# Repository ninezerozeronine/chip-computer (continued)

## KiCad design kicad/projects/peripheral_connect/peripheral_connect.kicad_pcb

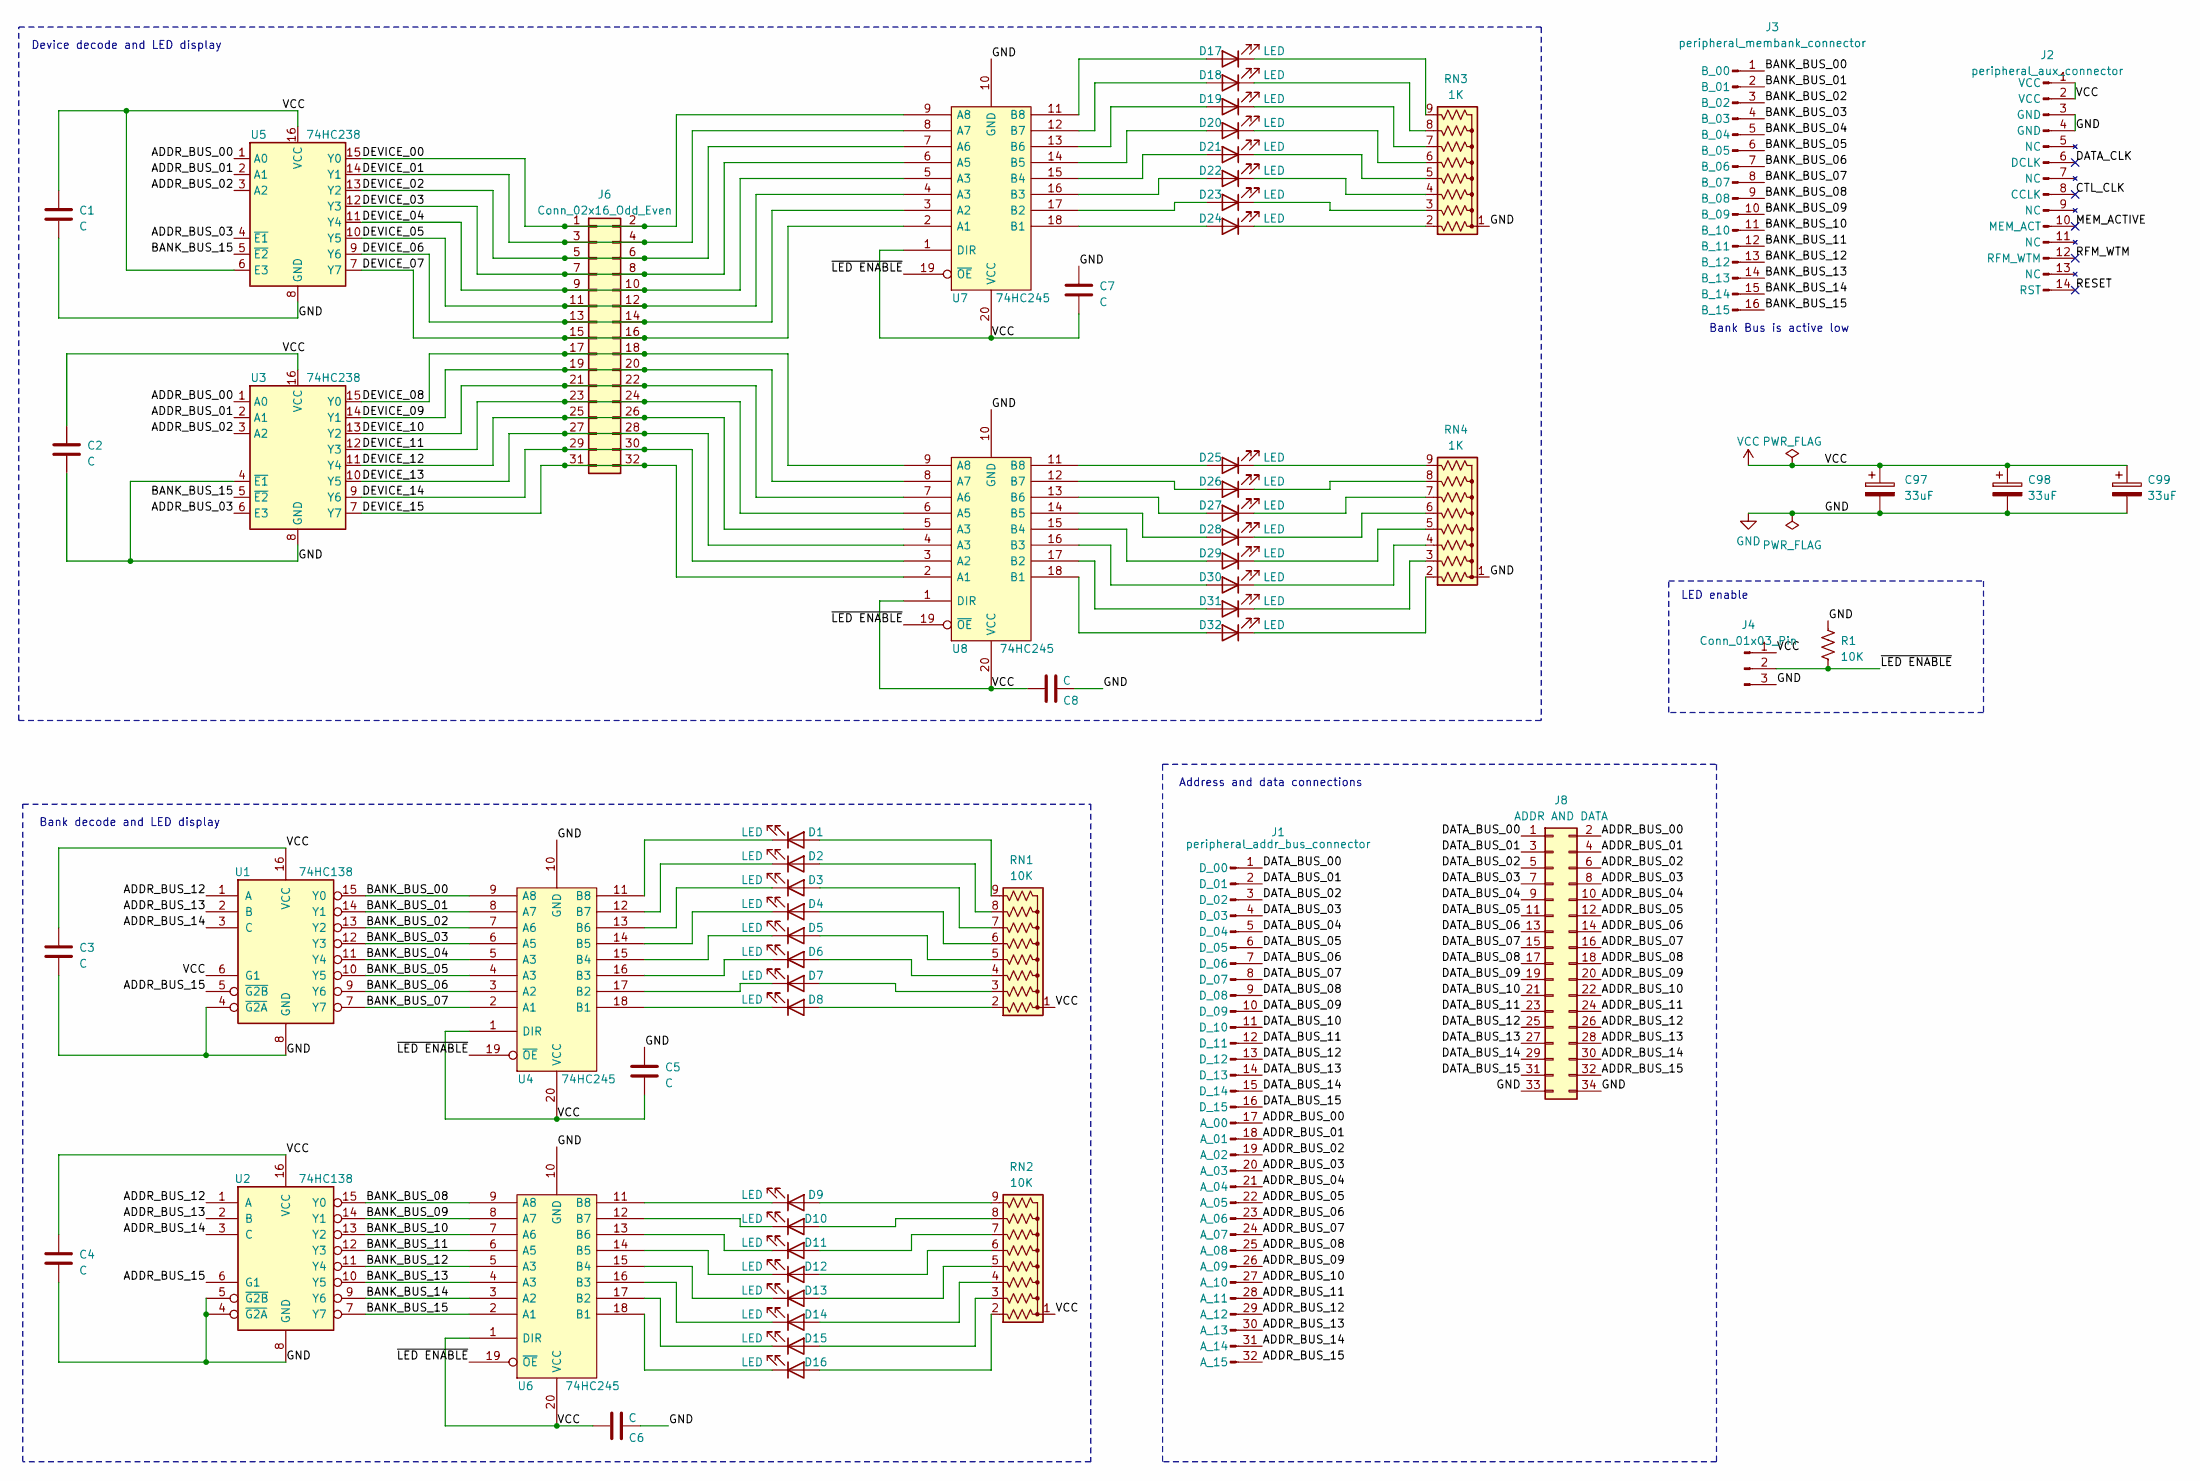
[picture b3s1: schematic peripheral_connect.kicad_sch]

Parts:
C1, C2, C3, C4, C5, C6, C7, C8: C; C_Disc_D5.0mm_W2.5mm_P5.00mm
C97, C98, C99: 33uF; CP_Radial_D6.3mm_P2.50mm
D1, D2, D3, D4, D5, D6, D7, D8, D9, D10, D11, D12, D13, D14, D15, D16, D17, D18, D19, D20, D21, D22, D23, D24, D25, D26, D27, D28, D29, D30, D31, D32: LED; LED_D5.0mm_Horizontal_O3.81mm_Z3.0mm
J1: peripheral_addr_bus_connector; peripheral-backplane-data-addr-anno
J2: peripheral_aux_connector; peripheral-backplane-aux
J3: peripheral_membank_connector; peripheral-backplane-membank
J4: Conn_01x03_Pin; PinHeader_1x03_P2.54mm_Horizontal
J6: Conn_02x16_Odd_Even; PinSocket_2x16_P2.54mm_Horizontal
J8: ADDR AND DATA; PinSocket_2x17_P2.54mm_Horizontal
R1: 10K; R_Axial_DIN0207_L6.3mm_D2.5mm_P10.16mm_Horizontal
RN1, RN2: 10K; R_Array_SIP9
RN3, RN4: 1K; R_Array_SIP9
U1, U2: 74HC138; DIP-16_W7.62mm_Socket
U3, U5: 74HC238; DIP-16_W7.62mm_Socket
U4, U6, U7, U8: 74HC245; DIP-20_W7.62mm_Socket

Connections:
/ADDR_BUS_00: J1.17 (A_00), J8.2, U3.1 (A0), U5.1 (A0)
/ADDR_BUS_01: J1.18 (A_01), J8.4, U3.2 (A1), U5.2 (A1)
/ADDR_BUS_02: J1.19 (A_02), J8.6, U3.3 (A2), U5.3 (A2)
/ADDR_BUS_03: J1.20 (A_03), J8.8, U3.6 (E3), U5.4 (~E1)
/ADDR_BUS_04: J1.21 (A_04), J8.10
/ADDR_BUS_05: J1.22 (A_05), J8.12
/ADDR_BUS_06: J1.23 (A_06), J8.14
/ADDR_BUS_07: J1.24 (A_07), J8.16
/ADDR_BUS_08: J1.25 (A_08), J8.18
/ADDR_BUS_09: J1.26 (A_09), J8.20
/ADDR_BUS_10: J1.27 (A_10), J8.22
/ADDR_BUS_11: J1.28 (A_11), J8.24
/ADDR_BUS_12: J1.29 (A_12), J8.26, U1.1 (A), U2.1 (A)
/ADDR_BUS_13: J1.30 (A_13), J8.28, U1.2 (B), U2.2 (B)
/ADDR_BUS_14: J1.31 (A_14), J8.30, U1.3 (C), U2.3 (C)
/ADDR_BUS_15: J1.32 (A_15), J8.32, U1.5 (~G2B), U2.6 (G1)
/BANK_BUS_00: J3.1 (B_00), U1.15 (Y0), U4.9 (A8)
/BANK_BUS_01: J3.2 (B_01), U1.14 (Y1), U4.8 (A7)
/BANK_BUS_02: J3.3 (B_02), U1.13 (Y2), U4.7 (A6)
/BANK_BUS_03: J3.4 (B_03), U1.12 (Y3), U4.6 (A5)
/BANK_BUS_04: J3.5 (B_04), U1.11 (Y4), U4.5 (A3)
/BANK_BUS_05: J3.6 (B_05), U1.10 (Y5), U4.4 (A3)
/BANK_BUS_06: J3.7 (B_06), U1.9 (Y6), U4.3 (A2)
/BANK_BUS_07: J3.8 (B_07), U1.7 (Y7), U4.2 (A1)
/BANK_BUS_08: J3.9 (B_08), U2.15 (Y0), U6.9 (A8)
/BANK_BUS_09: J3.10 (B_09), U2.14 (Y1), U6.8 (A7)
/BANK_BUS_10: J3.11 (B_10), U2.13 (Y2), U6.7 (A6)
/BANK_BUS_11: J3.12 (B_11), U2.12 (Y3), U6.6 (A5)
/BANK_BUS_12: J3.13 (B_12), U2.11 (Y4), U6.5 (A3)
/BANK_BUS_13: J3.14 (B_13), U2.10 (Y5), U6.4 (A3)
/BANK_BUS_14: J3.15 (B_14), U2.9 (Y6), U6.3 (A2)
/BANK_BUS_15: J3.16 (B_15), U2.7 (Y7), U3.5 (~E2), U5.5 (~E2), U6.2 (A1)
/CTL_CLK: J2.8 (CCLK)
/DATA_BUS_00: J1.1 (D_00), J8.1
/DATA_BUS_01: J1.2 (D_01), J8.3
/DATA_BUS_02: J1.3 (D_02), J8.5
/DATA_BUS_03: J1.4 (D_03), J8.7
/DATA_BUS_04: J1.5 (D_04), J8.9
/DATA_BUS_05: J1.6 (D_05), J8.11
/DATA_BUS_06: J1.7 (D_06), J8.13
/DATA_BUS_07: J1.8 (D_07), J8.15
/DATA_BUS_08: J1.9 (D_08), J8.17
/DATA_BUS_09: J1.10 (D_09), J8.19
/DATA_BUS_10: J1.11 (D_10), J8.21
/DATA_BUS_11: J1.12 (D_11), J8.23
/DATA_BUS_12: J1.13 (D_12), J8.25
/DATA_BUS_13: J1.14 (D_13), J8.27
/DATA_BUS_14: J1.15 (D_14), J8.29
/DATA_BUS_15: J1.16 (D_15), J8.31
/DATA_CLK: J2.6 (DCLK)
/DEVICE_00: J6.1, J6.2, U5.15 (Y0), U7.9 (A8)
/DEVICE_01: J6.3, J6.4, U5.14 (Y1), U7.8 (A7)
/DEVICE_02: J6.5, J6.6, U5.13 (Y2), U7.7 (A6)
/DEVICE_03: J6.7, J6.8, U5.12 (Y3), U7.6 (A5)
/DEVICE_04: J6.9, J6.10, U5.11 (Y4), U7.5 (A3)
/DEVICE_05: J6.11, J6.12, U5.10 (Y5), U7.4 (A3)
/DEVICE_06: J6.13, J6.14, U5.9 (Y6), U7.3 (A2)
/DEVICE_07: J6.15, J6.16, U5.7 (Y7), U7.2 (A1)
/DEVICE_08: J6.17, J6.18, U3.15 (Y0), U8.9 (A8)
/DEVICE_09: J6.19, J6.20, U3.14 (Y1), U8.8 (A7)
/DEVICE_10: J6.21, J6.22, U3.13 (Y2), U8.7 (A6)
/DEVICE_11: J6.23, J6.24, U3.12 (Y3), U8.6 (A5)
/DEVICE_12: J6.25, J6.26, U3.11 (Y4), U8.5 (A3)
/DEVICE_13: J6.27, J6.28, U3.10 (Y5), U8.4 (A3)
/DEVICE_14: J6.29, J6.30, U3.9 (Y6), U8.3 (A2)
/DEVICE_15: J6.31, J6.32, U3.7 (Y7), U8.2 (A1)
/MEM_ACTIVE: J2.10 (MEM_ACT)
/RESET: J2.14 (RST)
/RFM_WTM: J2.12 (RFM_WTM)
/~LED ENABLE: J4.2, R1.1, U4.19 (~OE), U6.19 (~OE), U7.19 (~OE), U8.19 (~OE)
GND: C1.2, C2.2, C3.2, C4.2, C5.2, C6.1, C7.2, C8.1, C97.2, C98.2, C99.2, J2.3 (GND), J2.4 (GND), J4.3, J8.33, J8.34, R1.2, RN3.1 (common), RN4.1 (common), U1.4 (~G2A), U1.8 (GND), U2.4 (~G2A), U2.5 (~G2B), U2.8 (GND), U3.4 (~E1), U3.8 (GND), U4.10 (GND), U5.8 (GND), U6.10 (GND), U7.10 (GND), U8.10 (GND)
unnamed: D1.2 (A), RN1.9 (R8)
unnamed: D1.1 (K), U4.11 (B8)
unnamed: D2.2 (A), RN1.8 (R7)
unnamed: D2.1 (K), U4.12 (B7)
unnamed: D3.2 (A), RN1.7 (R6)
unnamed: D3.1 (K), U4.13 (B6)
unnamed: D4.2 (A), RN1.6 (R5)
unnamed: D4.1 (K), U4.14 (B5)
unnamed: D5.2 (A), RN1.5 (R4)
unnamed: D5.1 (K), U4.15 (B4)
unnamed: D6.2 (A), RN1.4 (R3)
unnamed: D6.1 (K), U4.16 (B3)
unnamed: D7.2 (A), RN1.3 (R2)
unnamed: D7.1 (K), U4.17 (B2)
unnamed: D8.2 (A), RN1.2 (R1)
unnamed: D8.1 (K), U4.18 (B1)
unnamed: D9.2 (A), RN2.9 (R8)
unnamed: D9.1 (K), U6.11 (B8)
unnamed: D10.2 (A), RN2.8 (R7)
unnamed: D10.1 (K), U6.12 (B7)
unnamed: D11.2 (A), RN2.7 (R6)
unnamed: D11.1 (K), U6.13 (B6)
unnamed: D12.2 (A), RN2.6 (R5)
unnamed: D12.1 (K), U6.14 (B5)
unnamed: D13.2 (A), RN2.5 (R4)
unnamed: D13.1 (K), U6.15 (B4)
unnamed: D14.2 (A), RN2.4 (R3)
unnamed: D14.1 (K), U6.16 (B3)
unnamed: D15.2 (A), RN2.3 (R2)
unnamed: D15.1 (K), U6.17 (B2)
unnamed: D16.2 (A), RN2.2 (R1)
unnamed: D16.1 (K), U6.18 (B1)
unnamed: D17.2 (A), U7.11 (B8)
unnamed: D17.1 (K), RN3.9 (R8)
unnamed: D18.2 (A), U7.12 (B7)
unnamed: D18.1 (K), RN3.8 (R7)
unnamed: D19.2 (A), U7.13 (B6)
unnamed: D19.1 (K), RN3.7 (R6)
unnamed: D20.2 (A), U7.14 (B5)
unnamed: D20.1 (K), RN3.6 (R5)
unnamed: D21.2 (A), U7.15 (B4)
unnamed: D21.1 (K), RN3.5 (R4)
unnamed: D22.2 (A), U7.16 (B3)
unnamed: D22.1 (K), RN3.4 (R3)
unnamed: D23.2 (A), U7.17 (B2)
unnamed: D23.1 (K), RN3.3 (R2)
unnamed: D24.2 (A), U7.18 (B1)
unnamed: D24.1 (K), RN3.2 (R1)
unnamed: D25.2 (A), U8.11 (B8)
unnamed: D25.1 (K), RN4.9 (R8)
unnamed: D26.2 (A), U8.12 (B7)
unnamed: D26.1 (K), RN4.8 (R7)
unnamed: D27.2 (A), U8.13 (B6)
unnamed: D27.1 (K), RN4.7 (R6)
unnamed: D28.2 (A), U8.14 (B5)
unnamed: D28.1 (K), RN4.6 (R5)
unnamed: D29.2 (A), U8.15 (B4)
unnamed: D29.1 (K), RN4.5 (R4)
unnamed: D30.2 (A), U8.16 (B3)
unnamed: D30.1 (K), RN4.4 (R3)
unnamed: D31.2 (A), U8.17 (B2)
unnamed: D31.1 (K), RN4.3 (R2)
unnamed: D32.2 (A), U8.18 (B1)
unnamed: D32.1 (K), RN4.2 (R1)
VCC: C1.1, C2.1, C3.1, C4.1, C5.1, C6.2, C7.1, C8.2, C97.1, C98.1, C99.1, J2.1 (VCC), J2.2 (VCC), J4.1, RN1.1 (common), RN2.1 (common), U1.6 (G1), U1.16 (VCC), U2.16 (VCC), U3.16 (VCC), U4.1 (DIR), U4.20 (VCC), U5.6 (E3), U5.16 (VCC), U6.1 (DIR), U6.20 (VCC), U7.1 (DIR), U7.20 (VCC), U8.1 (DIR), U8.20 (VCC)

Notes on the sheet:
Address and data connections
Bank decode and LED display
Device decode and LED display
LED enable
Bank Bus is active low

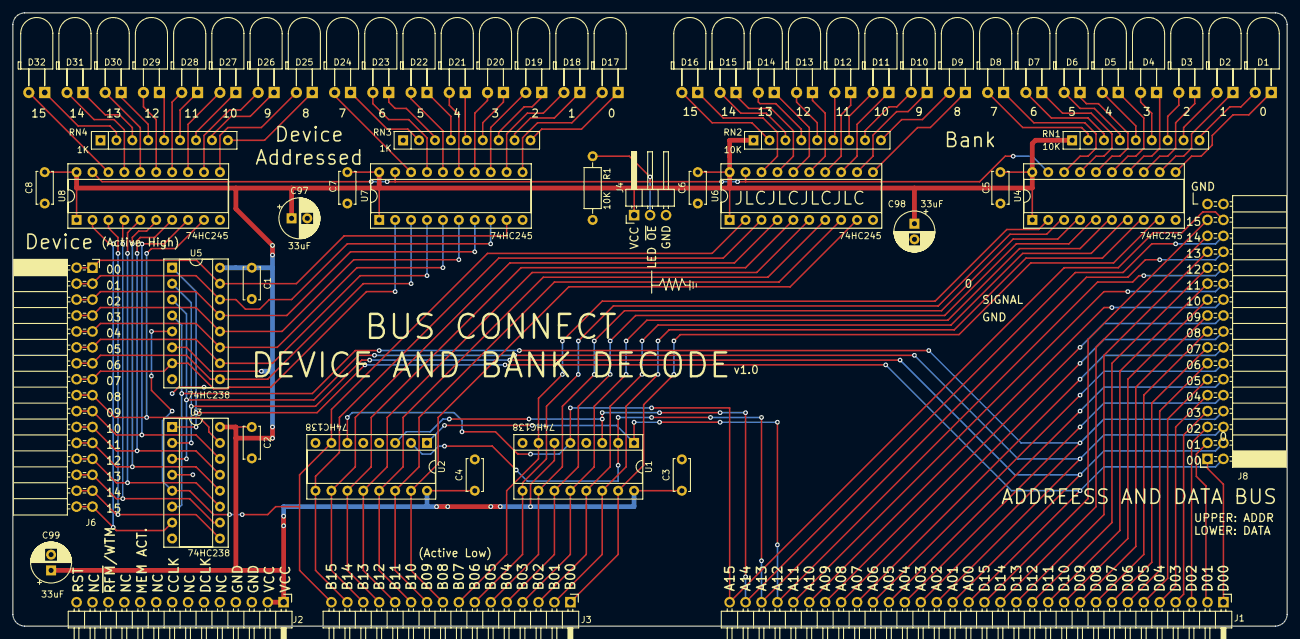
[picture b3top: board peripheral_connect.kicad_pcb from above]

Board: 2 copper layers, 203.2 x 97.8 mm, 62 parts (0 on the bottom side), 131 nets.

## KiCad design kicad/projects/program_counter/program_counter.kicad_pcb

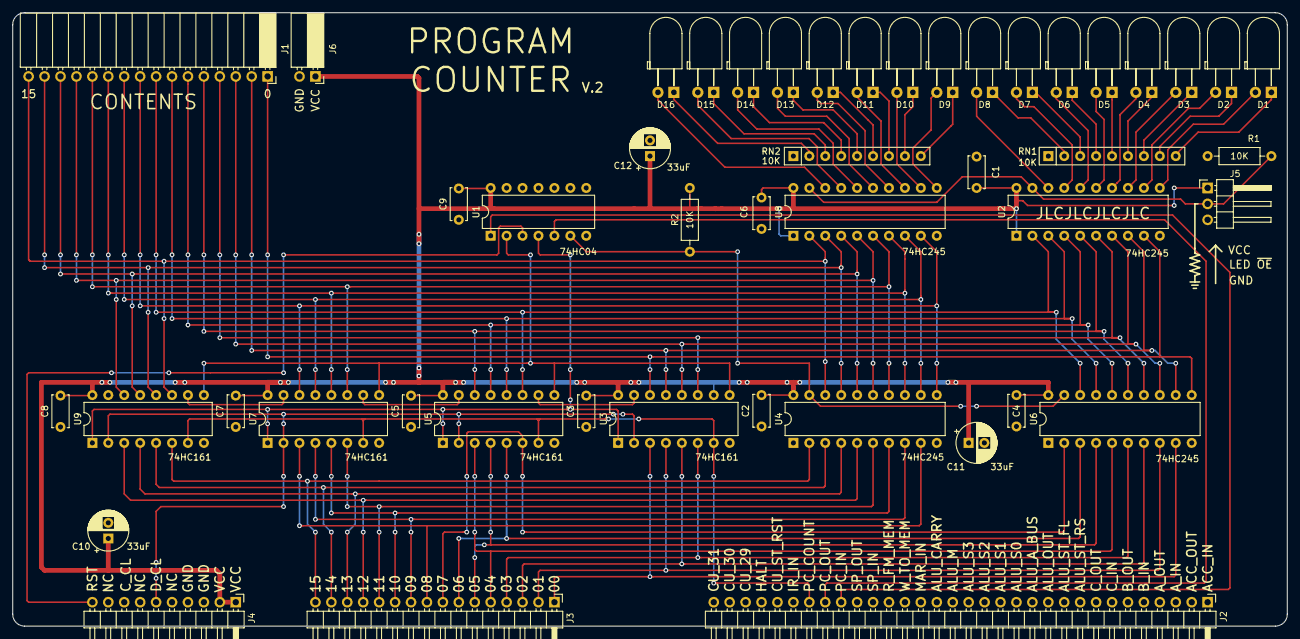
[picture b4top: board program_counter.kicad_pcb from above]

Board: 2 copper layers, 203.2 x 97.8 mm, 47 parts (0 on the bottom side), 78 nets.

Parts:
C1, C2, C3, C4, C5, C6, C7, C8, C9: 0.1uF; C_Disc_D5.0mm_W2.5mm_P5.00mm
C10, C11, C12: 33uF; CP_Radial_D6.3mm_P2.50mm
D1, D2, D3, D4, D5, D6, D7, D8, D9, D10, D11, D12, D13, D14, D15, D16: LED; LED_D5.0mm_Horizontal_O3.81mm_Z3.0mm
J1: Conn_01x16_Female; PinSocket_1x16_P2.54mm_Horizontal
J2: Control_signal_backplane; backplane-connector-single-row-annotated
J3: Bus_connection; bus-connection
J4: Aux_connection; aux-connection
J5: LED_CONTROL; PinHeader_1x03_P2.54mm_Horizontal
J6: TOP_POWER; PinSocket_1x02_P2.54mm_Horizontal
R1, R2: 10K; R_Axial_DIN0207_L6.3mm_D2.5mm_P10.16mm_Horizontal
RN1, RN2: 10K; R_Array_SIP9
U1: 74HC04; DIP-14_W7.62mm
U2, U4, U6, U8: 74HC245; DIP-20_W7.62mm
U3, U5, U7, U9: 74HC161; DIP-16_W7.62mm

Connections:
/BUS_00: J3.1, U3.3, U6.9
/BUS_01: J3.2, U3.4, U6.8
/BUS_02: J3.3, U3.5, U6.7
/BUS_03: J3.4, U3.6, U6.6
/BUS_04: J3.5, U5.3, U6.5
/BUS_05: J3.6, U5.4, U6.4
/BUS_06: J3.7, U5.5, U6.3
/BUS_07: J3.8, U5.6, U6.2
/BUS_08: J3.9, U4.9, U7.3
/BUS_09: J3.10, U4.8, U7.4
/BUS_10: J3.11, U4.7, U7.5
/BUS_11: J3.12, U4.6, U7.6
/BUS_12: J3.13, U4.5, U9.3
/BUS_13: J3.14, U4.4, U9.4
/BUS_14: J3.15, U4.3, U9.5
/BUS_15: J3.16, U4.2, U9.6
/CTNT_00: J1.1, U2.9, U3.14, U6.11
/CTNT_01: J1.2, U2.8, U3.13, U6.12
/CTNT_02: J1.3, U2.7, U3.12, U6.13
/CTNT_03: J1.4, U2.6, U3.11, U6.14
/CTNT_04: J1.5, U2.5, U5.14, U6.15
/CTNT_05: J1.6, U2.4, U5.13, U6.16
/CTNT_06: J1.7, U2.3, U5.12, U6.17
/CTNT_07: J1.8, U2.2, U5.11, U6.18
/CTNT_08: J1.9, U4.11, U7.14, U8.9
/CTNT_09: J1.10, U4.12, U7.13, U8.8
/CTNT_10: J1.11, U4.13, U7.12, U8.7
/CTNT_11: J1.12, U4.14, U7.11, U8.6
/CTNT_12: J1.13, U4.15, U8.5, U9.14
/CTNT_13: J1.14, U4.16, U8.4, U9.13
/CTNT_14: J1.15, U4.17, U8.3, U9.12
/CTNT_15: J1.16, U4.18, U8.2, U9.11
/DATA_CLK: J4.6, U3.2, U5.2, U7.2, U9.2
/LED_CONTROL: J5.2, R1.1, U2.19, U8.19
/PC_COUNT: J2.26, U3.7, U5.7, U7.7, U9.7
/PC_IN: J2.24, U1.1
/PC_OUT: J2.25, U1.5
/RESET: J4.10, U1.3
/~PC_IN: U1.2, U3.9, U5.9, U7.9, U9.9
/~PC_OUT: R2.1, U1.6, U4.19, U6.19
/~RESET: U1.4, U3.1, U5.1, U7.1, U9.1
GND: C1.2, C2.2, C3.1, C4.2, C5.1, C6.2, C7.1, C8.1, C9.1, C10.2, C11.2, C12.2, J4.3, J4.4, J5.3, J6.2, R1.2, RN1.1, RN2.1, U1.7, U1.9, U1.11, U1.13, U2.10, U3.8, U4.1, U4.10, U5.8, U6.1, U6.10, U7.8, U8.10, U9.8
unnamed: D1.1, RN1.9
unnamed: D1.2, U2.11
unnamed: D2.1, RN1.8
unnamed: D2.2, U2.12
unnamed: D3.1, RN1.7
unnamed: D3.2, U2.13
unnamed: D4.1, RN1.6
unnamed: D4.2, U2.14
unnamed: D5.1, RN1.5
unnamed: D5.2, U2.15
unnamed: D6.1, RN1.4
unnamed: D6.2, U2.16
unnamed: D7.1, RN1.3
unnamed: D7.2, U2.17
unnamed: D8.1, RN1.2
unnamed: D8.2, U2.18
unnamed: D9.1, RN2.9
unnamed: D9.2, U8.11
unnamed: D10.1, RN2.8
unnamed: D10.2, U8.12
unnamed: D11.1, RN2.7
unnamed: D11.2, U8.13
unnamed: D12.1, RN2.6
unnamed: D12.2, U8.14
unnamed: D13.1, RN2.5
unnamed: D13.2, U8.15
unnamed: D14.1, RN2.4
unnamed: D14.2, U8.16
unnamed: D15.1, RN2.3
unnamed: D15.2, U8.17
unnamed: D16.1, RN2.2
unnamed: D16.2, U8.18
unnamed: U3.15, U5.10
unnamed: U5.15, U7.10
unnamed: U7.15, U9.10
VCC: C1.1, C2.1, C3.2, C4.1, C5.2, C6.1, C7.2, C8.2, C9.2, C10.1, C11.1, C12.1, J4.1, J4.2, J5.1, J6.1, R2.2, U1.14, U2.1, U2.20, U3.10, U3.16, U4.20, U5.16, U6.20, U7.16, U8.1, U8.20, U9.16

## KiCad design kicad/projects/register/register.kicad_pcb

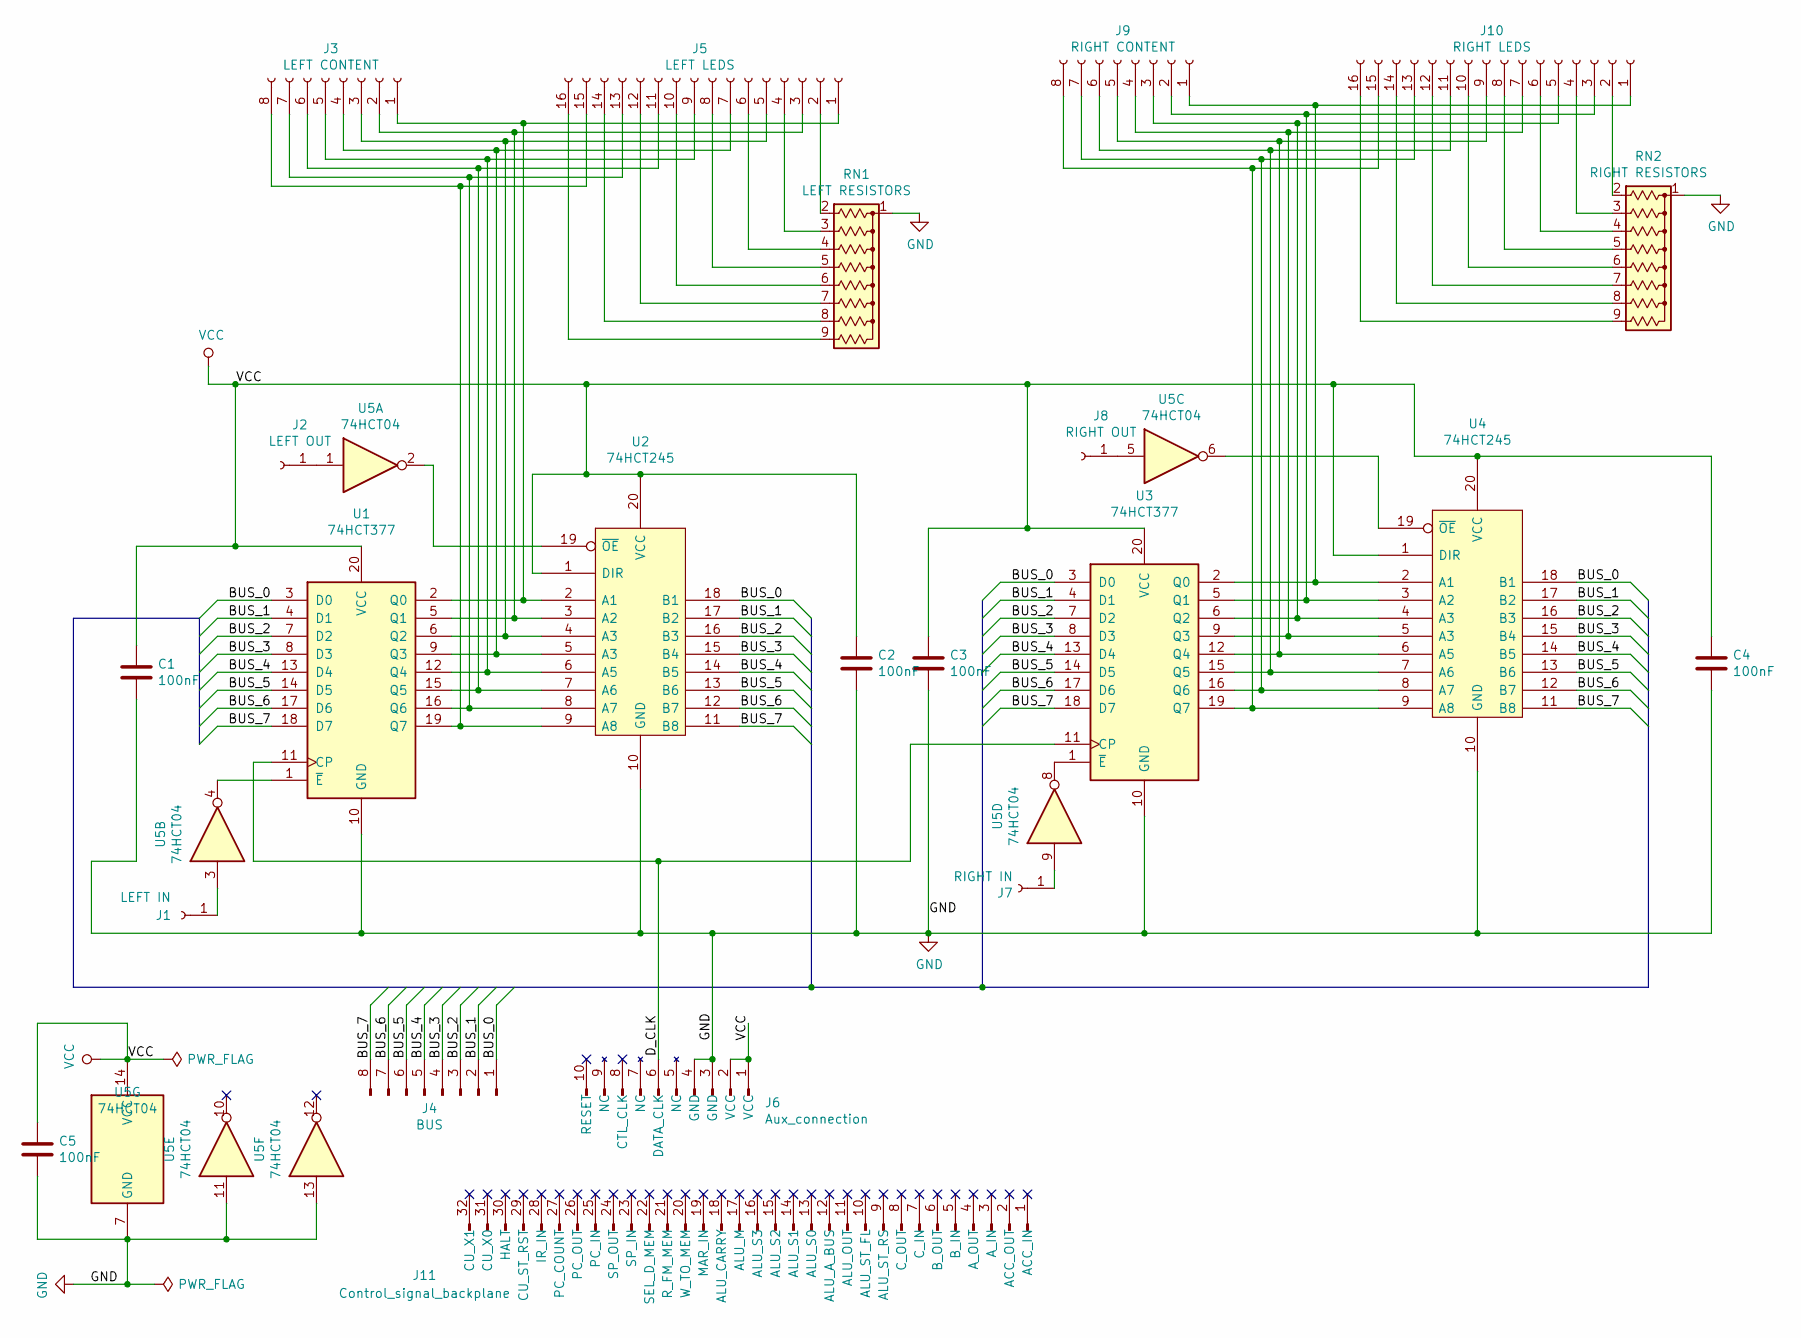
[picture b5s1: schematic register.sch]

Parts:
C1, C2, C3, C4, C5: 100nF; C_Disc_D4.7mm_W2.5mm_P5.00mm
J1: LEFT IN; SolderWirePad_1x01_Drill0.8mm
J2: LEFT OUT; SolderWirePad_1x01_Drill0.8mm
J3: LEFT CONTENT; PinSocket_1x08_P2.54mm_Horizontal
J4: BUS; PinHeader_1x08_P2.54mm_Horizontal
J5: LEFT LEDS; PinSocket_1x16_P2.54mm_Horizontal
J6: Aux_connection; PinHeader_1x10_P2.54mm_Horizontal
J7: RIGHT IN; SolderWirePad_1x01_Drill0.8mm
J8: RIGHT OUT; SolderWirePad_1x01_Drill0.8mm
J9: RIGHT CONTENT; PinSocket_1x08_P2.54mm_Horizontal
J10: RIGHT LEDS; PinSocket_1x16_P2.54mm_Horizontal
J11: Control_signal_backplane; backplane-connector
RN1: LEFT RESISTORS; R_Array_SIP9
RN2: RIGHT RESISTORS; R_Array_SIP9
U1, U3: 74HCT377; DIP-20_W7.62mm_Socket
U2, U4: 74HCT245; DIP-20_W7.62mm_Socket
U5: 74HCT04; DIP-14_W7.62mm_Socket

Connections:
/BUS_0: J4.1, U1.3 (D0), U2.18 (B1), U3.3 (D0), U4.18 (B1)
/BUS_1: J4.2, U1.4 (D1), U2.17 (B2), U3.4 (D1), U4.17 (B2)
/BUS_2: J4.3, U1.7 (D2), U2.16 (B3), U3.7 (D2), U4.16 (B3)
/BUS_3: J4.4, U1.8 (D3), U2.15 (B4), U3.8 (D3), U4.15 (B4)
/BUS_4: J4.5, U1.13 (D4), U2.14 (B5), U3.13 (D4), U4.14 (B5)
/BUS_5: J4.6, U1.14 (D5), U2.13 (B6), U3.14 (D5), U4.13 (B6)
/BUS_6: J4.7, U1.17 (D6), U2.12 (B7), U3.17 (D6), U4.12 (B7)
/BUS_7: J4.8, U1.18 (D7), U2.11 (B8), U3.18 (D7), U4.11 (B8)
/D_CLK: J6.6 (DATA_CLK), U1.11 (CP), U3.11 (CP)
GND: C1.2, C2.2, C3.2, C4.2, C5.2, J6.3 (GND), J6.4 (GND), RN1.1 (common), RN2.1 (common), U1.10 (GND), U2.10 (GND), U3.10 (GND), U4.10 (GND), U5.7 (GND), U5.11, U5.13
unnamed: J1.1, U5.3
unnamed: J2.1, U5.1
unnamed: J3.1, J5.1, U1.2 (Q0), U2.2 (A1)
unnamed: J3.2, J5.3, U1.5 (Q1), U2.3 (A2)
unnamed: J3.3, J5.5, U1.6 (Q2), U2.4 (A3)
unnamed: J3.4, J5.7, U1.9 (Q3), U2.5 (A3)
unnamed: J3.5, J5.9, U1.12 (Q4), U2.6 (A5)
unnamed: J3.6, J5.11, U1.15 (Q5), U2.7 (A6)
unnamed: J3.7, J5.13, U1.16 (Q6), U2.8 (A7)
unnamed: J3.8, J5.15, U1.19 (Q7), U2.9 (A8)
unnamed: J5.2, RN1.2 (R1)
unnamed: J5.4, RN1.3 (R2)
unnamed: J5.6, RN1.4 (R3)
unnamed: J5.8, RN1.5 (R4)
unnamed: J5.10, RN1.6 (R5)
unnamed: J5.12, RN1.7 (R6)
unnamed: J5.14, RN1.8 (R7)
unnamed: J5.16, RN1.9 (R8)
unnamed: J7.1, U5.9
unnamed: J8.1, U5.5
unnamed: J9.1, J10.1, U3.2 (Q0), U4.2 (A1)
unnamed: J10.2, RN2.2 (R1)
unnamed: J9.2, J10.3, U3.5 (Q1), U4.3 (A2)
unnamed: J10.4, RN2.3 (R2)
unnamed: J9.3, J10.5, U3.6 (Q2), U4.4 (A3)
unnamed: J10.6, RN2.4 (R3)
unnamed: J9.4, J10.7, U3.9 (Q3), U4.5 (A3)
unnamed: J10.8, RN2.5 (R4)
unnamed: J9.5, J10.9, U3.12 (Q4), U4.6 (A5)
unnamed: J10.10, RN2.6 (R5)
unnamed: J9.6, J10.11, U3.15 (Q5), U4.7 (A6)
unnamed: J10.12, RN2.7 (R6)
unnamed: J9.7, J10.13, U3.16 (Q6), U4.8 (A7)
unnamed: J10.14, RN2.8 (R7)
unnamed: J9.8, J10.15, U3.19 (Q7), U4.9 (A8)
unnamed: J10.16, RN2.9 (R8)
unnamed: U1.1 (~E), U5.4
unnamed: U2.19 (~OE), U5.2
unnamed: U3.1 (~E), U5.8
unnamed: U4.19 (~OE), U5.6
VCC: C1.1, C2.1, C3.1, C4.1, C5.1, J6.1 (VCC), J6.2 (VCC), U1.20 (VCC), U2.1 (DIR), U2.20 (VCC), U3.20 (VCC), U4.1 (DIR), U4.20 (VCC), U5.14 (VCC)

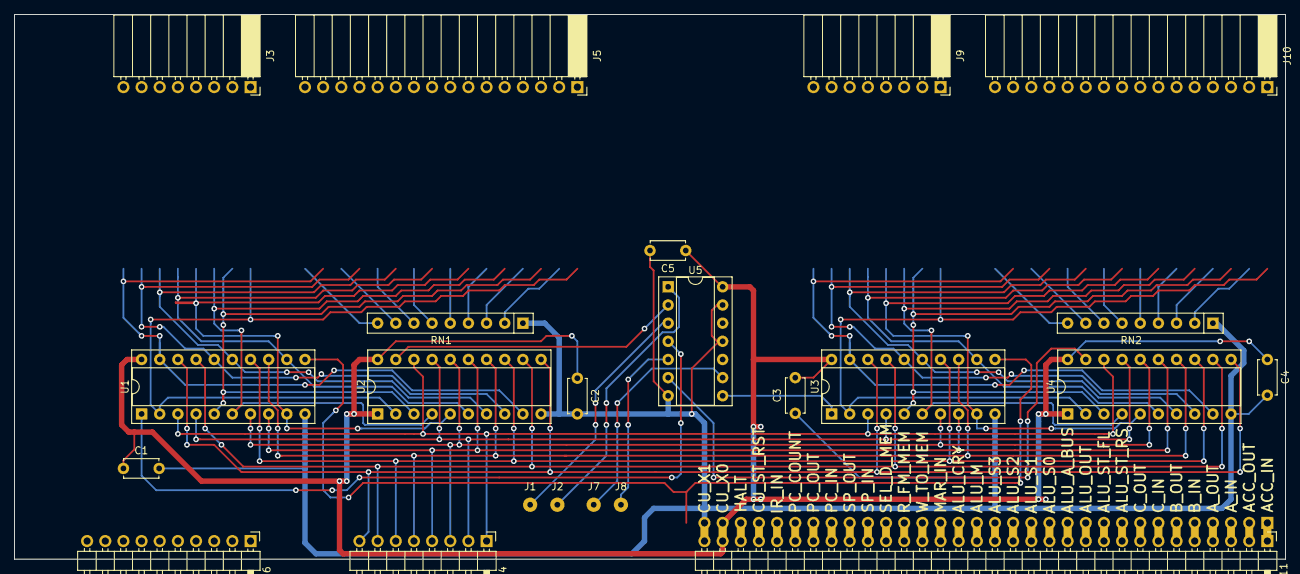
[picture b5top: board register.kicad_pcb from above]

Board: 2 copper layers, 177.8 x 76.2 mm, 23 parts (0 on the bottom side), 51 nets.

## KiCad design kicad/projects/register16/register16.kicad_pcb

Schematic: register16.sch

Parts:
C1, C2, C3, C4, C5, C6, C7: 0.1uF; C_Disc_D4.3mm_W1.9mm_P5.00mm
C8, C9, C10: 33uF; CP_Radial_D6.3mm_P2.50mm
D1, D2, D3, D4, D5, D6, D7, D8, D9, D10, D11, D12, D13, D14, D15, D16: LED; LED_D5.0mm_Horizontal_O3.81mm_Z3.0mm
J1: INPUT_ENABLE; SolderWirePad_1x01_Drill1mm
J2: OUTPUT_ENABLE; SolderWirePad_1x01_Drill1mm
J3: CONTENTS; PinSocket_1x16_P2.54mm_Horizontal
J4: Control_signal_backplane; backplane-connector-annotated
J5: Aux_connection; aux-connection
J6: Bus_connection; bus-connection
J7, J9: HIGH; SolderWirePad_1x01_Drill1mm
J8, J10: LOW; SolderWirePad_1x01_Drill1mm
J11: LED_CONTROL; PinHeader_1x03_P2.54mm_Horizontal
J12: TOP_POWER; PinSocket_1x02_P2.54mm_Horizontal
R1, R2: 10K; R_Axial_DIN0207_L6.3mm_D2.5mm_P10.16mm_Horizontal
RN1, RN2: R_Network08_US; R_Array_SIP9
U1: 74HC04; DIP-14_W7.62mm_Socket
U2, U3: 74HC377; DIP-20_W7.62mm_Socket
U4, U5, U6, U7: 74HC245; DIP-20_W7.62mm_Socket

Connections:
/BUF00: D1.2 (A), U7.11 (B8)
/BUF01: D2.2 (A), U7.12 (B7)
/BUF02: D3.2 (A), U7.13 (B6)
/BUF03: D4.2 (A), U7.14 (B5)
/BUF04: D5.2 (A), U7.15 (B4)
/BUF05: D6.2 (A), U7.16 (B3)
/BUF06: D7.2 (A), U7.17 (B2)
/BUF07: D8.2 (A), U7.18 (B1)
/BUF08: D9.2 (A), U6.11 (B8)
/BUF09: D10.2 (A), U6.12 (B7)
/BUF10: D11.2 (A), U6.13 (B6)
/BUF11: D12.2 (A), U6.14 (B5)
/BUF12: D13.2 (A), U6.15 (B4)
/BUF13: D14.2 (A), U6.16 (B3)
/BUF14: D15.2 (A), U6.17 (B2)
/BUF15: D16.2 (A), U6.18 (B1)
/BUS00: J6.1 (BUS_00), U3.18 (D7), U5.9 (A8)
/BUS01: J6.2 (BUS_01), U3.17 (D6), U5.8 (A7)
/BUS02: J6.3 (BUS_02), U3.14 (D5), U5.7 (A6)
/BUS03: J6.4 (BUS_03), U3.13 (D4), U5.6 (A5)
/BUS04: J6.5 (BUS_04), U3.8 (D3), U5.5 (A3)
/BUS05: J6.6 (BUS_05), U3.7 (D2), U5.4 (A3)
/BUS06: J6.7 (BUS_06), U3.4 (D1), U5.3 (A2)
/BUS07: J6.8 (BUS_07), U3.3 (D0), U5.2 (A1)
/BUS08: J6.9 (BUS_08), U2.18 (D7), U4.9 (A8)
/BUS09: J6.10 (BUS_09), U2.17 (D6), U4.8 (A7)
/BUS10: J6.11 (BUS_10), U2.14 (D5), U4.7 (A6)
/BUS11: J6.12 (BUS_11), U2.13 (D4), U4.6 (A5)
/BUS12: J6.13 (BUS_12), U2.8 (D3), U4.5 (A3)
/BUS13: J6.14 (BUS_13), U2.7 (D2), U4.4 (A3)
/BUS14: J6.15 (BUS_14), U2.4 (D1), U4.3 (A2)
/BUS15: J6.16 (BUS_15), U2.3 (D0), U4.2 (A1)
/CNT00: J3.1, U3.19 (Q7), U5.11 (B8), U7.9 (A8)
/CNT01: J3.2, U3.16 (Q6), U5.12 (B7), U7.8 (A7)
/CNT02: J3.3, U3.15 (Q5), U5.13 (B6), U7.7 (A6)
/CNT03: J3.4, U3.12 (Q4), U5.14 (B5), U7.6 (A5)
/CNT04: J3.5, U3.9 (Q3), U5.15 (B4), U7.5 (A3)
/CNT05: J3.6, U3.6 (Q2), U5.16 (B3), U7.4 (A3)
/CNT06: J3.7, U3.5 (Q1), U5.17 (B2), U7.3 (A2)
/CNT07: J3.8, U3.2 (Q0), U5.18 (B1), U7.2 (A1)
/CNT08: J3.9, U2.19 (Q7), U4.11 (B8), U6.9 (A8)
/CNT09: J3.10, U2.16 (Q6), U4.12 (B7), U6.8 (A7)
/CNT10: J3.11, U2.15 (Q5), U4.13 (B6), U6.7 (A6)
/CNT11: J3.12, U2.12 (Q4), U4.14 (B5), U6.6 (A5)
/CNT12: J3.13, U2.9 (Q3), U4.15 (B4), U6.5 (A3)
/CNT13: J3.14, U2.6 (Q2), U4.16 (B3), U6.4 (A3)
/CNT14: J3.15, U2.5 (Q1), U4.17 (B2), U6.3 (A2)
/CNT15: J3.16, U2.2 (Q0), U4.18 (B1), U6.2 (A1)
/DATA_CLK: J5.6 (DATA_CLK), U2.11 (CP), U3.11 (CP)
/LED_CONTROL: J11.2, R1.1, U6.19 (~OE), U7.19 (~OE)
GND: C1.2, C2.2, C3.2, C4.2, C5.2, C6.2, C7.2, C8.2, C9.2, C10.2, J5.3 (GND), J5.4 (GND), J8.1, J10.1, J11.3, J12.2, R1.2, RN1.1 (common), RN2.1 (common), U1.5, U1.7 (GND), U1.9, U1.11, U1.13, U2.10 (GND), U3.10 (GND), U4.1 (DIR), U4.10 (GND), U5.1 (DIR), U5.10 (GND), U6.10 (GND), U7.10 (GND)
unnamed: D1.1 (K), RN1.2 (R1)
unnamed: D2.1 (K), RN1.3 (R2)
unnamed: D3.1 (K), RN1.4 (R3)
unnamed: D4.1 (K), RN1.5 (R4)
unnamed: D5.1 (K), RN1.6 (R5)
unnamed: D6.1 (K), RN1.7 (R6)
unnamed: D7.1 (K), RN1.8 (R7)
unnamed: D8.1 (K), RN1.9 (R8)
unnamed: D9.1 (K), RN2.2 (R1)
unnamed: D10.1 (K), RN2.3 (R2)
unnamed: D11.1 (K), RN2.4 (R3)
unnamed: D12.1 (K), RN2.5 (R4)
unnamed: D13.1 (K), RN2.6 (R5)
unnamed: D14.1 (K), RN2.7 (R6)
unnamed: D15.1 (K), RN2.8 (R7)
unnamed: D16.1 (K), RN2.9 (R8)
unnamed: J1.1, U1.1
unnamed: J2.1, U1.3
unnamed: R2.2, U1.4, U4.19 (~OE), U5.19 (~OE)
unnamed: U1.2, U2.1 (~E), U3.1 (~E)
VCC: C1.1, C2.1, C3.1, C4.1, C5.1, C6.1, C7.1, C8.1, C9.1, C10.1, J5.1 (VCC), J5.2 (VCC), J7.1, J9.1, J11.1, J12.1, R2.1, U1.14 (VCC), U2.20 (VCC), U3.20 (VCC), U4.20 (VCC), U5.20 (VCC), U6.1 (DIR), U6.20 (VCC), U7.1 (DIR), U7.20 (VCC)

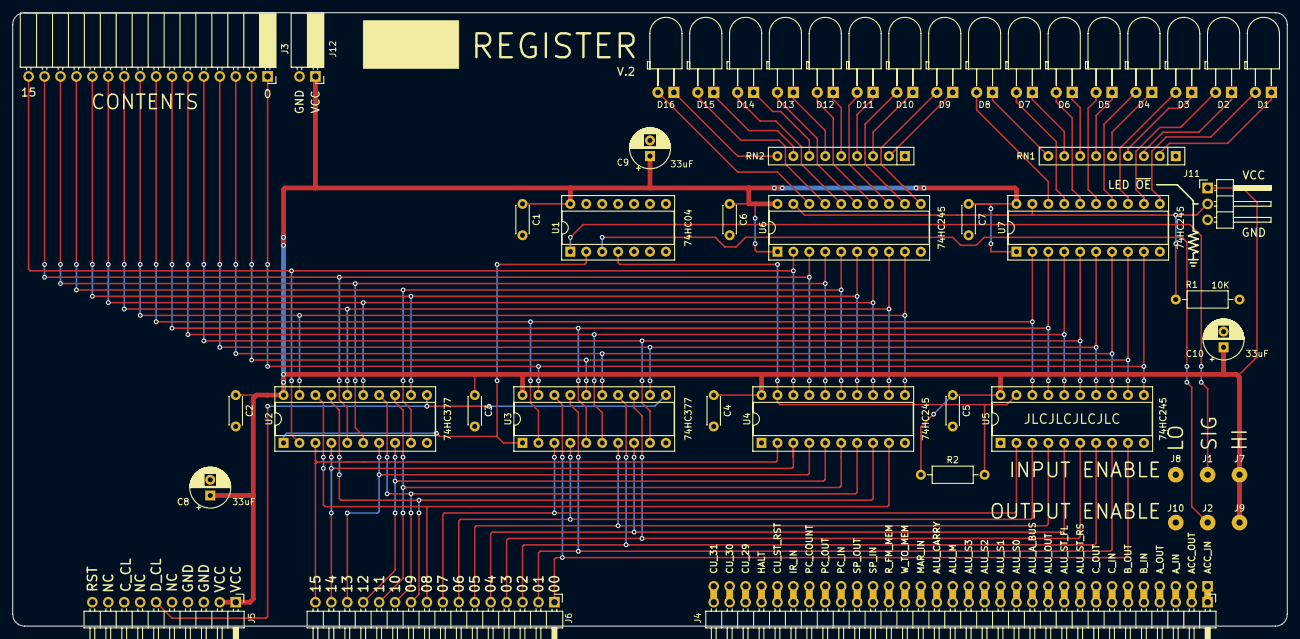
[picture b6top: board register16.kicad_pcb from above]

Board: 2 copper layers, 203.2 x 97.8 mm, 49 parts (0 on the bottom side), 72 nets.
